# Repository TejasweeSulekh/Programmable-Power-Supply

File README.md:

# Programmable-Power-Supply
## Electronic Design Lab - Spring Semester 2022 - Indian Institute of Technology
## Prof Joseph John, Prof Shiladri Chakraborty & Prof Siddharth Tallur

Made by
- Tejaswee Sulekh
- Bhavya Singh
- Shristi Sharma

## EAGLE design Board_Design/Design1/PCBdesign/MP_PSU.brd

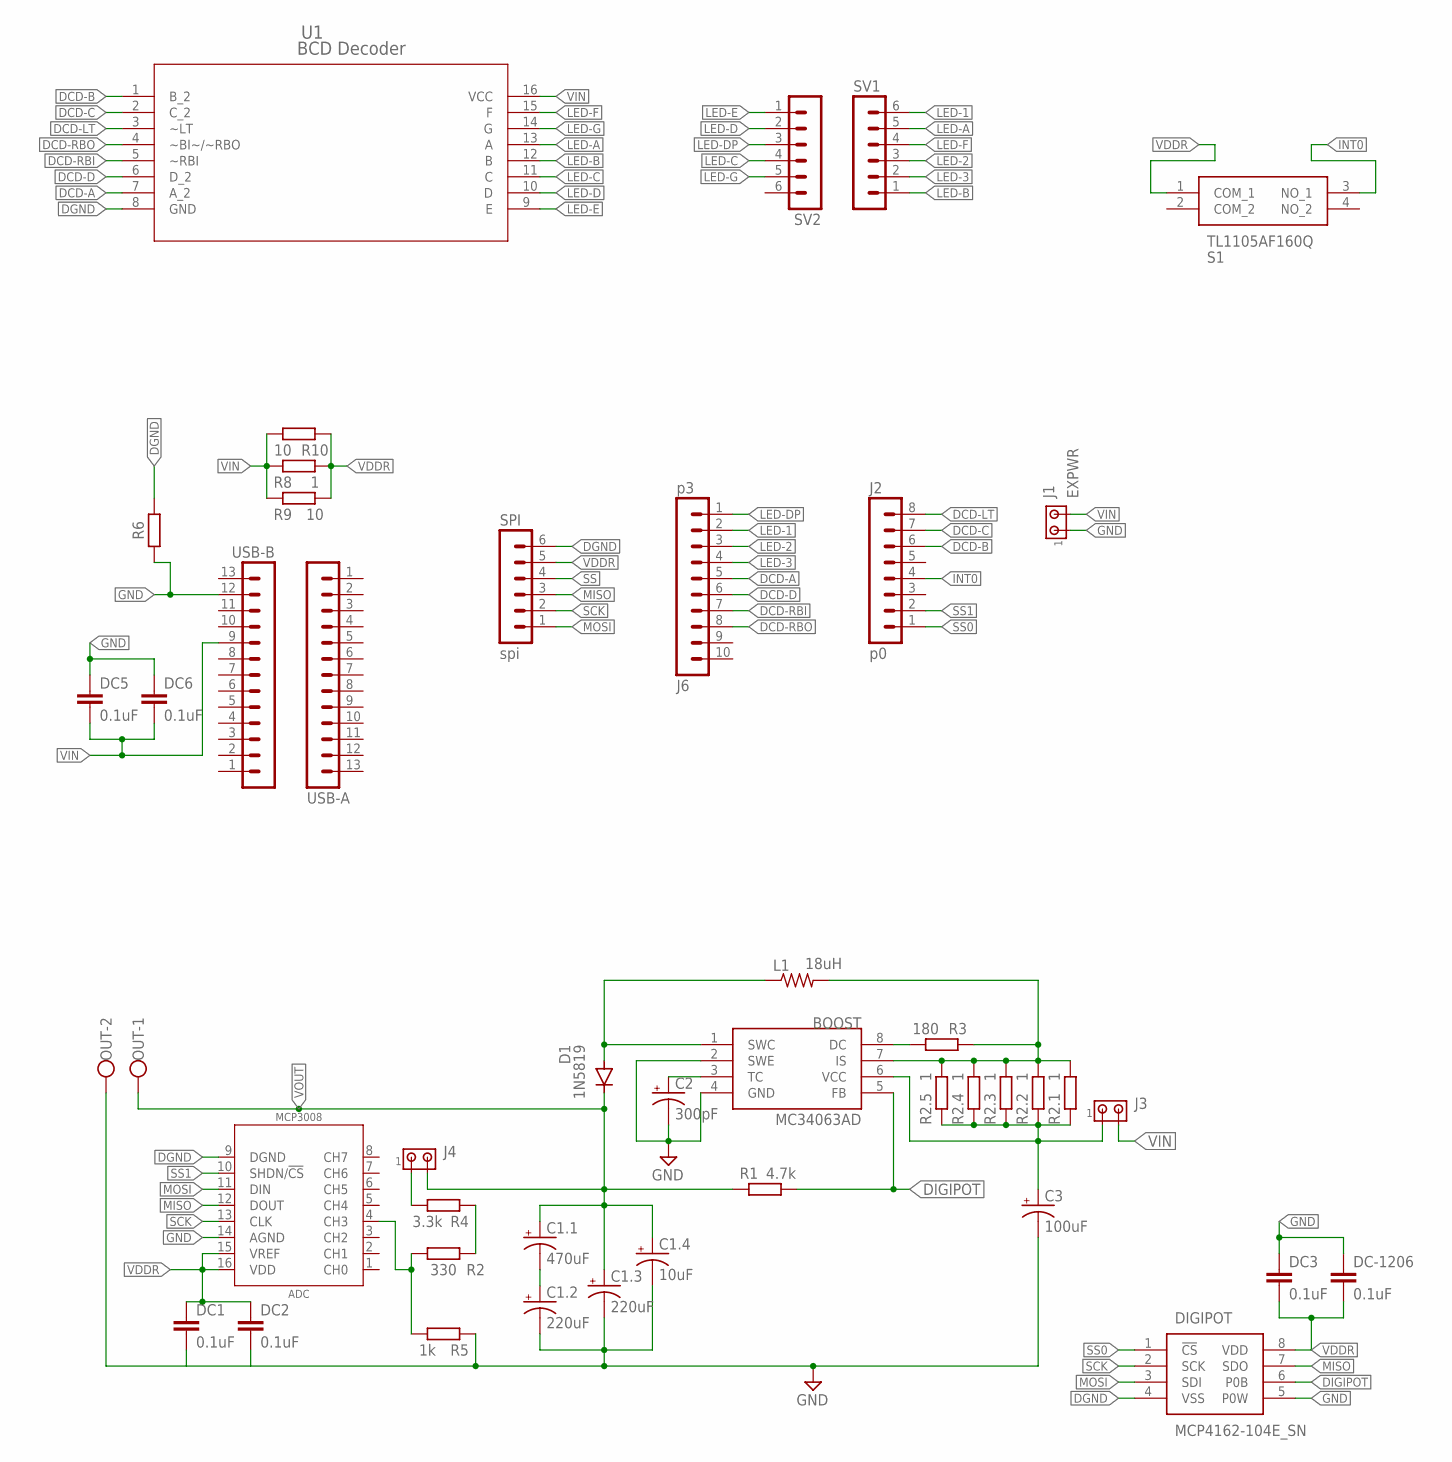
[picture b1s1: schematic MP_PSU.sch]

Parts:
ADC: MCP3008; DIP1092W56P254L1905H432Q16B
BOOST: MC34063AD; SOIC8
C1.1: 470uF; E2,5-6
C1.2, C1.3: 220uF; E2,5-6
C1.4: 10uF; E2,5-6
C2: 300pF; E2,5-6
C3: 100uF; E2,5-6
D1: 1N5819; DO41-10
DC1, DC2, DC3, DC5, DC6: 0.1uF; C1206
DC-1206: 0.1uF; C1206
DIGIPOT: MCP4162-104E_SN; SOIC127P600X175-8N
J1: EXPWR; 10X02MTA
J2: p0; MA08-1
J3, J4: MTA02-100; 10X02MTA
J6: p3; MA10-1
L1: 18uH; 0207/10
OUT: W237-102
R1: 4.7k; RESAD724W46L381D178B
R2: 330; RESAD724W46L381D178B
R2.1, R2.2, R2.3, R2.4, R2.5, R8: 1; RESAD724W46L381D178B
R3: 180; RESAD724W46L381D178B
R4: 3.3k; RESAD724W46L381D178B
R5: 1k; RESAD724W46L381D178B
R6: R_AXIAL-7.2MM-PITCH; RESAD724W46L381D178B
R9, R10: 10; RESAD724W46L381D178B
S1: TL1105AF160Q
SPI: spi; MA06-1
SV1, SV2: MA06-1
U1: BCD Decoder; DIP16_300
USB-A: MA13-1
USB-B: MA13-1

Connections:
B-VIN: BOOST.6 (VCC), C3.+, J3.1, R2.1.1, R2.2.1, R2.3.1, R2.4.1, R2.5.1
DCD-A: J6.5, U1.7 (A_2)
DCD-B: J2.6, U1.1 (B_2)
DCD-C: J2.7, U1.2 (C_2)
DCD-D: J6.6, U1.6 (D_2)
DCD-LT: J2.8, U1.3 (~LT)
DCD-RBI: J6.7, U1.5 (~RBI)
DCD-RBO: J6.8, U1.4 (~BI~/~RBO)
DGND: ADC.9 (DGND), DIGIPOT.4 (VSS), R6.1, SPI.6, U1.8 (GND)
DIGIPOT: BOOST.5 (FB), DIGIPOT.6 (P0B), R1.2
GND: ADC.14 (AGND), BOOST.2 (SWE), BOOST.4 (GND), C1.2.-, C1.3.-, C1.4.-, C2.-, C3.-, DC3.1, DC5.1, DC6.1, DC-1206.1, DIGIPOT.5 (P0W), J1.1, OUT.2, R5.1, R6.2, USB-B.12
GND1: DC1.2, DC2.2
INT0: J2.4, S1.3 (NO_1)
LED-1: J6.2, SV1.6
LED-2: J6.3, SV1.3
LED-3: J6.4, SV1.2
LED-A: SV1.5, U1.13 (A)
LED-B: SV1.1, U1.12 (B)
LED-C: SV2.4, U1.11 (C)
LED-D: SV2.2, U1.10 (D)
LED-DP: J6.1, SV2.3
LED-E: SV2.1, U1.9 (E)
LED-F: SV1.4, U1.15 (F)
LED-G: SV2.5, U1.14 (G)
MISO: ADC.12 (DOUT), DIGIPOT.7 (SDO), SPI.3
MOSI: ADC.11 (DIN), DIGIPOT.3 (SDI), SPI.1
unnamed: BOOST.7 (IS), L1.2, R2.1.2, R2.2.2, R2.3.2, R2.4.2, R2.5.2, R3.2
unnamed: BOOST.8 (DC), R3.1
unnamed: BOOST.1 (SWC), D1.A, L1.1
unnamed: BOOST.3 (TC), C2.+
unnamed: J4.1, R4.2
unnamed: C1.1.-, C1.2.+
unnamed: R2.1, R4.1
unnamed: ADC.4 (CH3), R2.2, R5.2
SCK: ADC.13 (CLK), DIGIPOT.2 (SCK), SPI.2
SS: SPI.4
SS0: DIGIPOT.1 (!CS), J2.1
SS1: ADC.10 (SHDN/!CS), J2.2
VDDR: ADC.15 (VREF), ADC.16 (VDD), DC1.1, DC2.1, DC3.2, DC-1206.2, DIGIPOT.8 (VDD), R8.2, R9.2, R10.2, S1.1 (COM_1), SPI.5
VIN: DC5.2, DC6.2, J1.2, J3.2, R8.1, R9.1, R10.1, U1.16 (VCC), USB-B.9
VOUT: C1.1.+, C1.3.+, C1.4.+, D1.C, J4.2, OUT.1, R1.1

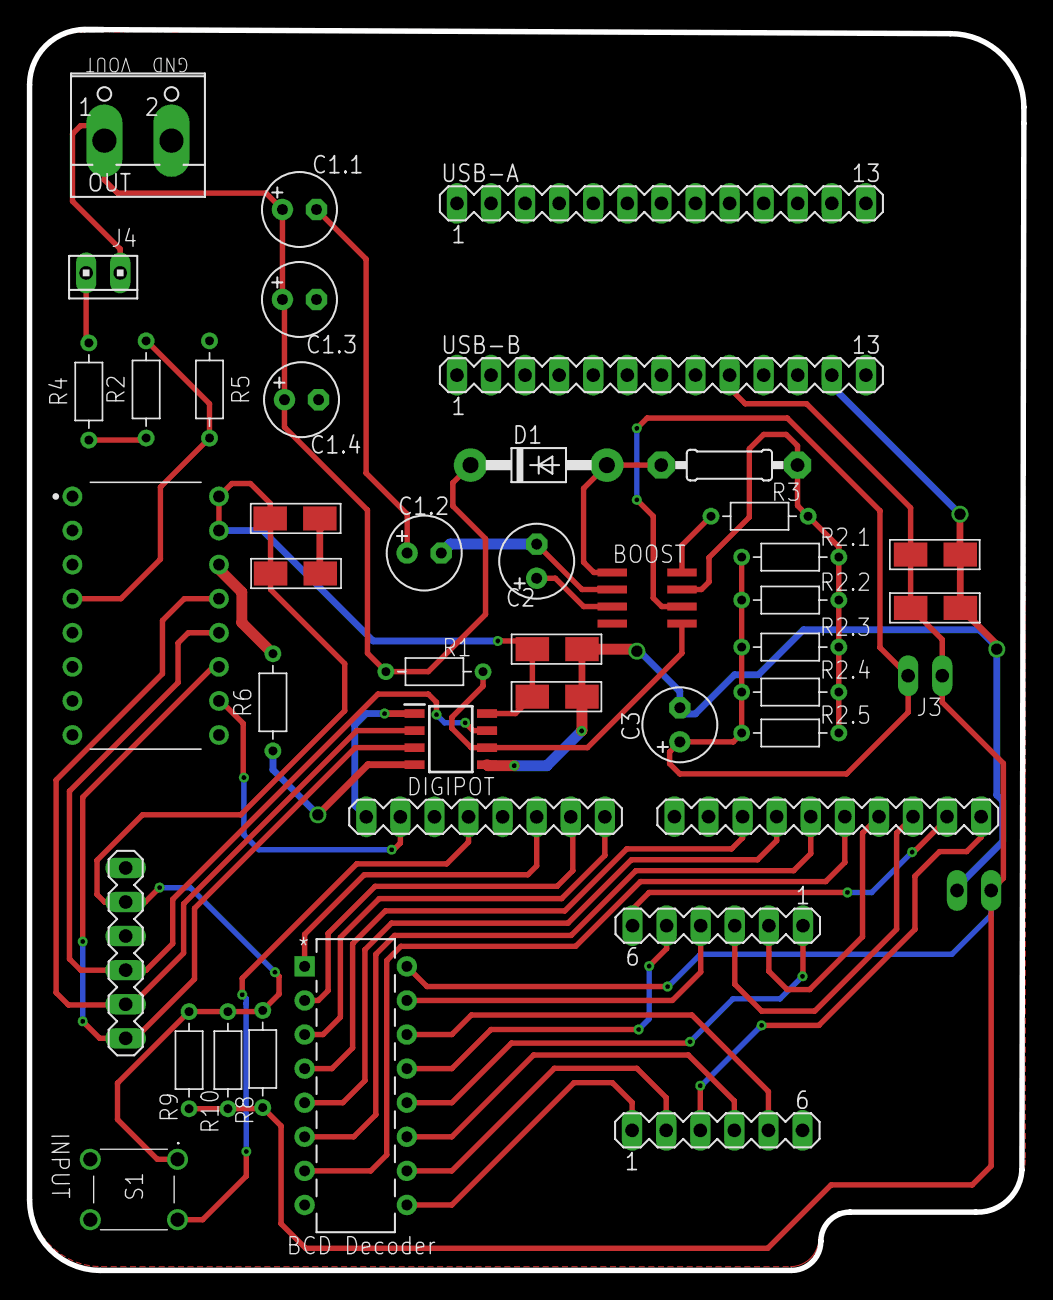
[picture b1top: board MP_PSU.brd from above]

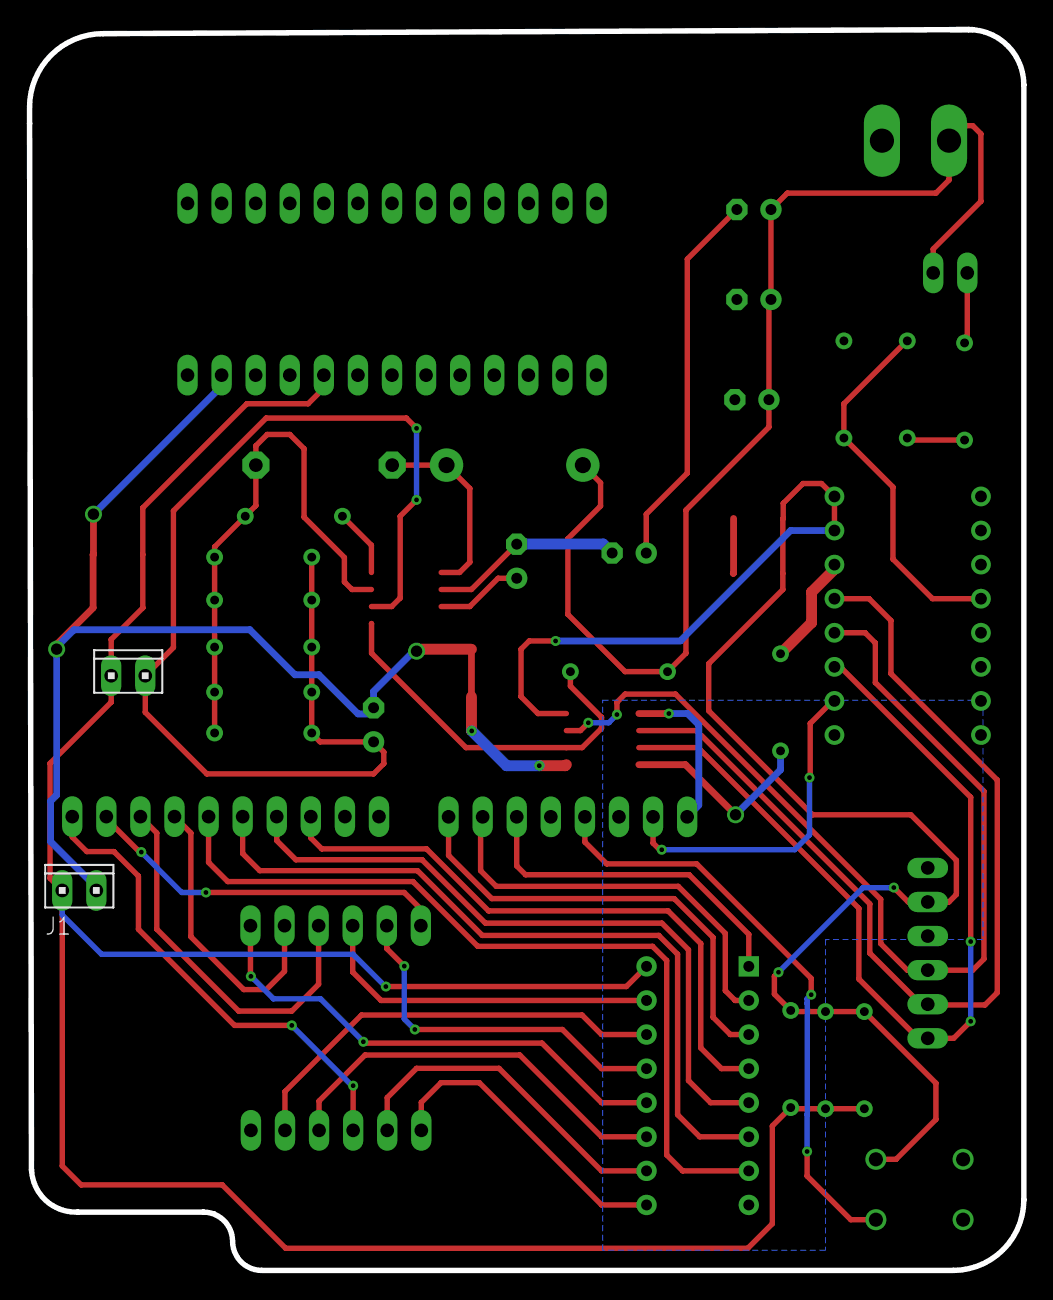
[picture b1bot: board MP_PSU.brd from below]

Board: 2 copper layers, 74.1 x 92.5 mm, 44 parts (2 on the bottom side), 40 nets.

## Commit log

2024-03-09 Added Readme
2024-03-09 Added a readme
2024-03-09 Added files

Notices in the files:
parts and their libraries:
COPYRIGHT: Copyright (C) 2023 Ultra Librarian. All rights reserved.
